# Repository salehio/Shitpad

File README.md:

# Shitpad
Quick and dirty PCB design to practice/PoC some keyboard stuff

- 4 regular switches
- 2 rotary encoders sharing a pin
- Elite-Pi MCU
- Broken out all pins to headers to help prototype other components
- 2 diodes in parallel to test out differences between TH and SMD
- 2 PCBs can be combined into a larger KB using i2c available through TRRS or USB-Micro

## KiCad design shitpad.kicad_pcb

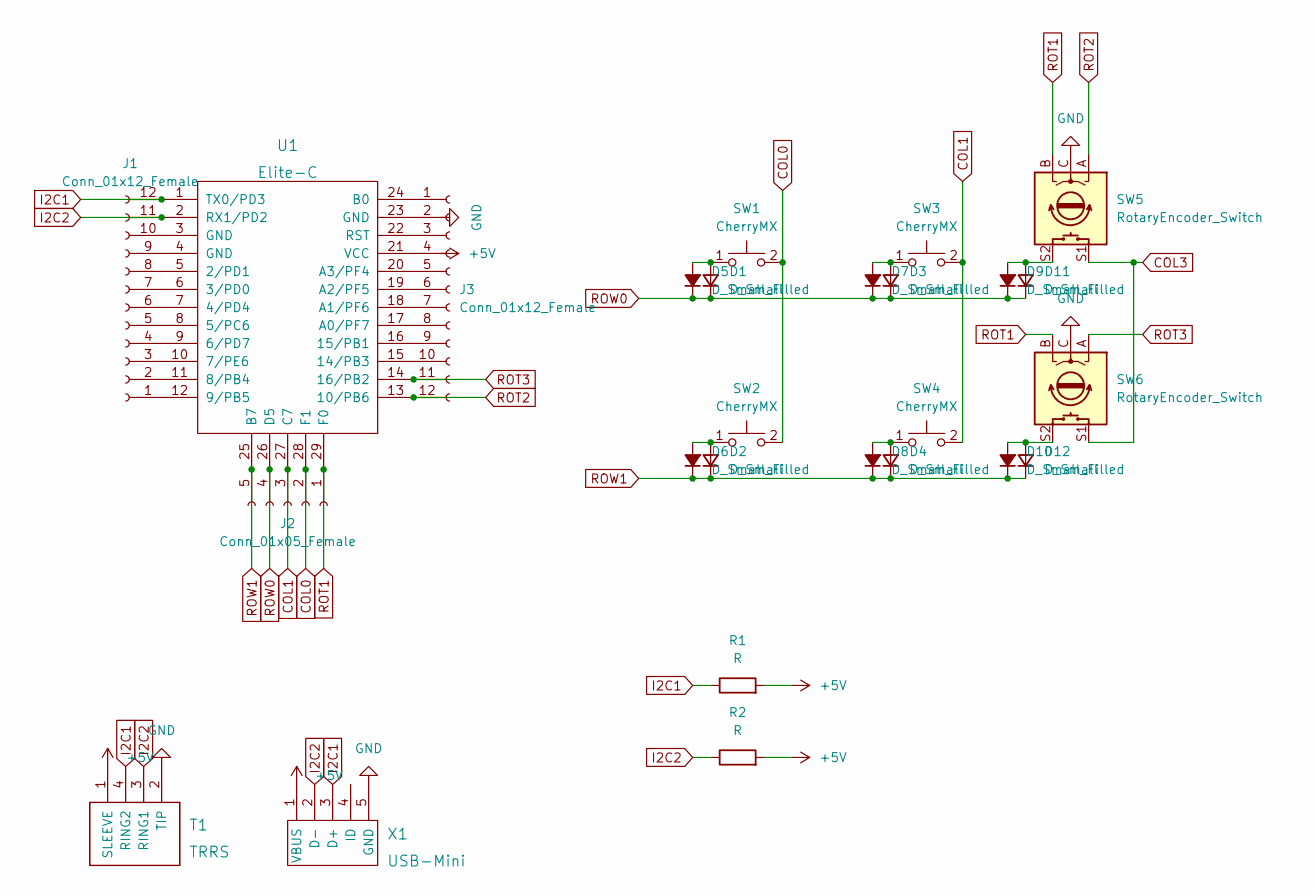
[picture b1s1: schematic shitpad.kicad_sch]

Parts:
D1, D2, D3, D4, D11, D12: D_Small; D_SOD-123
D5, D6, D7, D8, D9, D10: D_Small_Filled; D_DO-34_SOD68_P10.16mm_Horizontal
J1, J3: Conn_01x12_Female; PinHeader_1x12_P2.54mm_Vertical
J2: Conn_01x05_Female; PinHeader_1x05_P2.54mm_Vertical
R1, R2: R; R_Axial_DIN0204_L3.6mm_D1.6mm_P7.62mm_Horizontal
SW1, SW2, SW3, SW4: CherryMX; CherryMX_1.00u
SW5, SW6: RotaryEncoder_Switch; RotaryEncoder_Alps_EC11E-Switch_Vertical_H20mm
T1: TRRS; TRRS-PJ-320A
U1: Elite-C; Elite-C-ZigZag
X1: USB-Mini; PinHeader_1x05_P2.54mm_Vertical

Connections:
+5V: R1.2, R2.2, T1.1 (SLEEVE), X1.1 (VBUS)
COL0: J2.2, SW1.2, SW2.2, U1.28 (F1)
COL1: J2.3, SW3.2, SW4.2, U1.27 (C7)
COL3: SW5.S1, SW6.S1
GND: SW5.C, SW6.C, T1.2 (TIP), X1.5 (GND)
I2C1: J1.12, R1.1, T1.4 (RING2), U1.1 (TX0/PD3), X1.3 (D+)
I2C2: J1.11, R2.1, T1.3 (RING1), U1.2 (RX1/PD2), X1.2 (D-)
unnamed: D1.2 (A), D5.2 (A), SW1.1
unnamed: D2.2 (A), D6.2 (A), SW2.1
unnamed: D3.2 (A), D7.2 (A), SW3.1
unnamed: D4.2 (A), D8.2 (A), SW4.1
unnamed: D10.2 (A), D12.2 (A), SW6.S2
unnamed: J3.1, U1.24 (B0)
unnamed: J3.2, U1.23 (GND)
unnamed: J3.3, U1.22 (RST)
unnamed: J3.4, U1.21 (VCC)
unnamed: J3.5, U1.20 (A3/PF4)
unnamed: J3.6, U1.19 (A2/PF5)
unnamed: J3.7, U1.18 (A1/PF6)
unnamed: J3.8, U1.17 (A0/PF7)
unnamed: J3.9, U1.16 (15/PB1)
unnamed: J3.10, U1.15 (14/PB3)
unnamed: D9.2 (A), D11.2 (A), SW5.S2
unnamed: J1.10, U1.3 (GND)
unnamed: J1.9, U1.4 (GND)
unnamed: J1.8, U1.5 (2/PD1)
unnamed: J1.7, U1.6 (3/PD0)
unnamed: J1.6, U1.7 (4/PD4)
unnamed: J1.5, U1.8 (5/PC6)
unnamed: J1.4, U1.9 (6/PD7)
unnamed: J1.3, U1.10 (7/PE6)
unnamed: J1.2, U1.11 (8/PB4)
unnamed: J1.1, U1.12 (9/PB5)
ROT1: J2.1, SW5.B, SW6.B, U1.29 (F0)
ROT2: J3.12, SW5.A, U1.13 (10/PB6)
ROT3: J3.11, SW6.A, U1.14 (16/PB2)
ROW0: D1.1 (K), D3.1 (K), D5.1 (K), D7.1 (K), D9.1 (K), D11.1 (K), J2.4, U1.26 (D5)
ROW1: D2.1 (K), D4.1 (K), D6.1 (K), D8.1 (K), D10.1 (K), D12.1 (K), J2.5, U1.25 (B7)

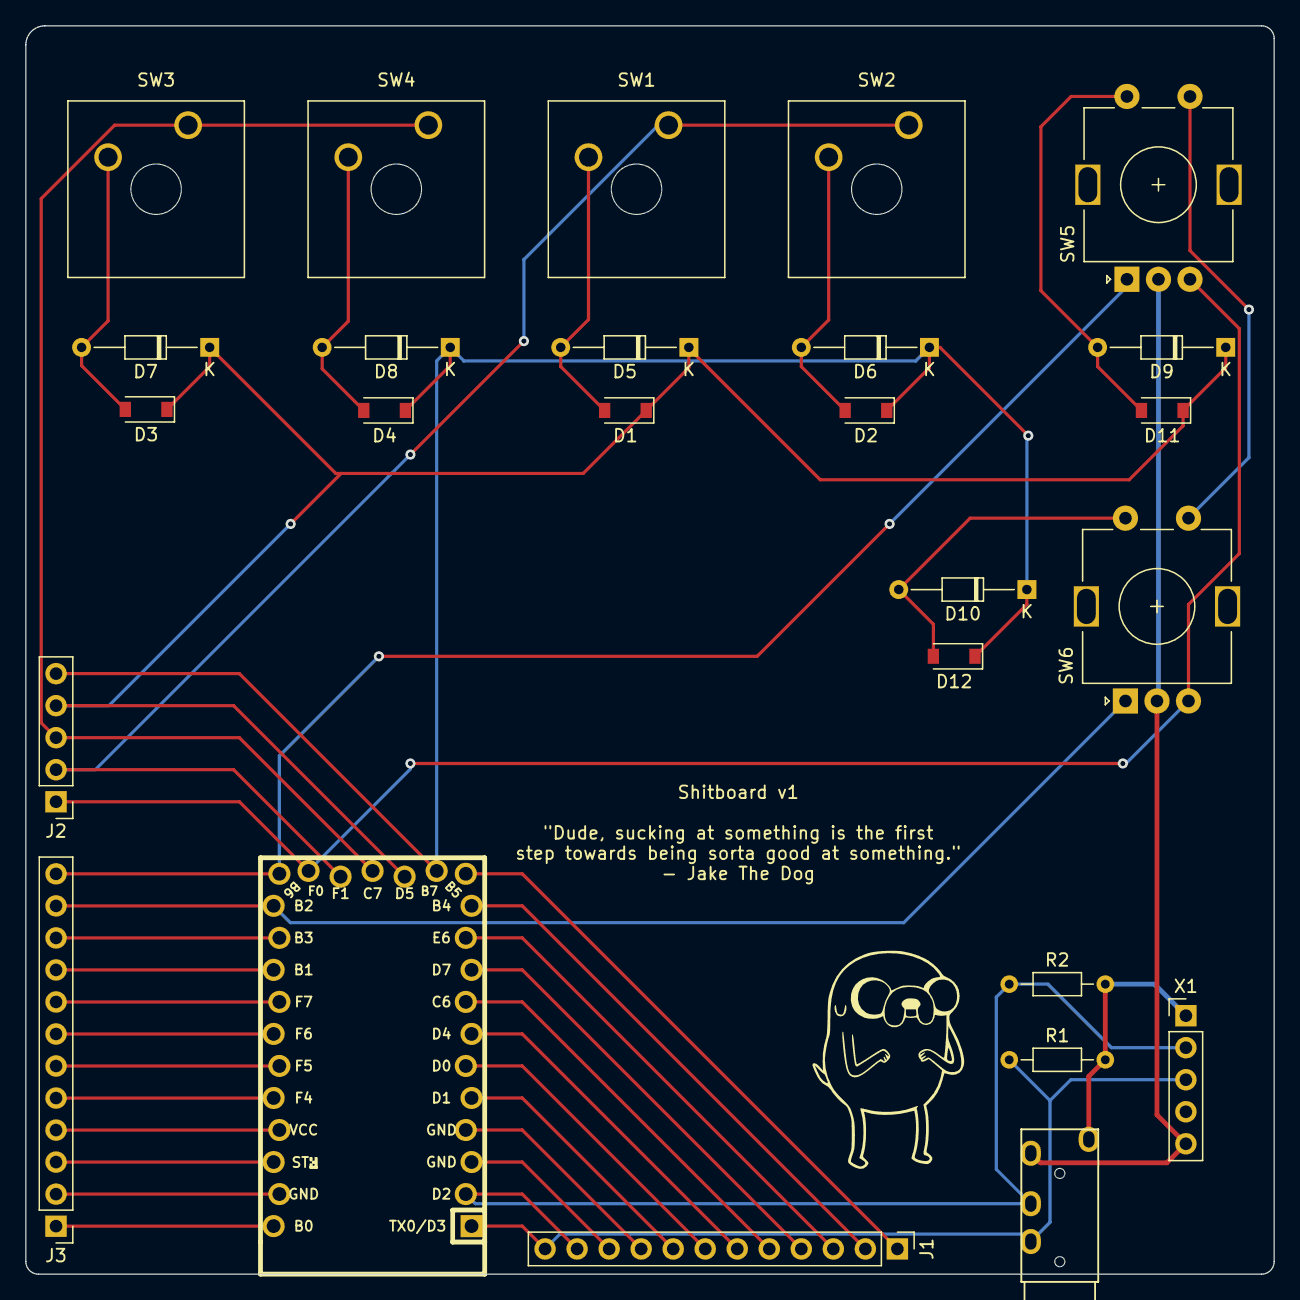
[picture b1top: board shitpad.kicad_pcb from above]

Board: 2 copper layers, 99.0 x 99.0 mm, 26 parts (0 on the bottom side), 38 nets.

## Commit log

2023-01-19 Initial commit of shitpad
